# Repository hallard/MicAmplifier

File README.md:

Universal Stereo MIC/Line amplifier for Audio processing with ADC
================================================================

This is a simple board to amplifiy stereo mic or ligne signal to be processed
by a analog entry of a microcontroller.

It can be used for processing audio and lit LED strip for example or whatever,
the input signal can come from electret microphone, standard microphone,
line out or any jack audio output of any device.

Schematics were strongly took and inspired from [coolarduino][1] site 
and the [vu meter 1][2] [vu meter 2][3] topic and schematics

Check out news and other projects on my [blog][4]

Detailed Description
====================

Everything will be documented on my[blog][4]

**Schematic**  

**Board**  

&nbsp;&nbsp;

[1]: http://coolarduino.wordpress.com/
[2]: http://coolarduino.wordpress.com/2012/06/28/stereo-audio-vu-meter-on-arduino/
[3]: http://coolarduino.wordpress.com/2012/07/01/audio-vu-meter-ac-micro-voltmeter-with-extra-wide-dynamic-range-72-db/
[4]: http://hallard.me

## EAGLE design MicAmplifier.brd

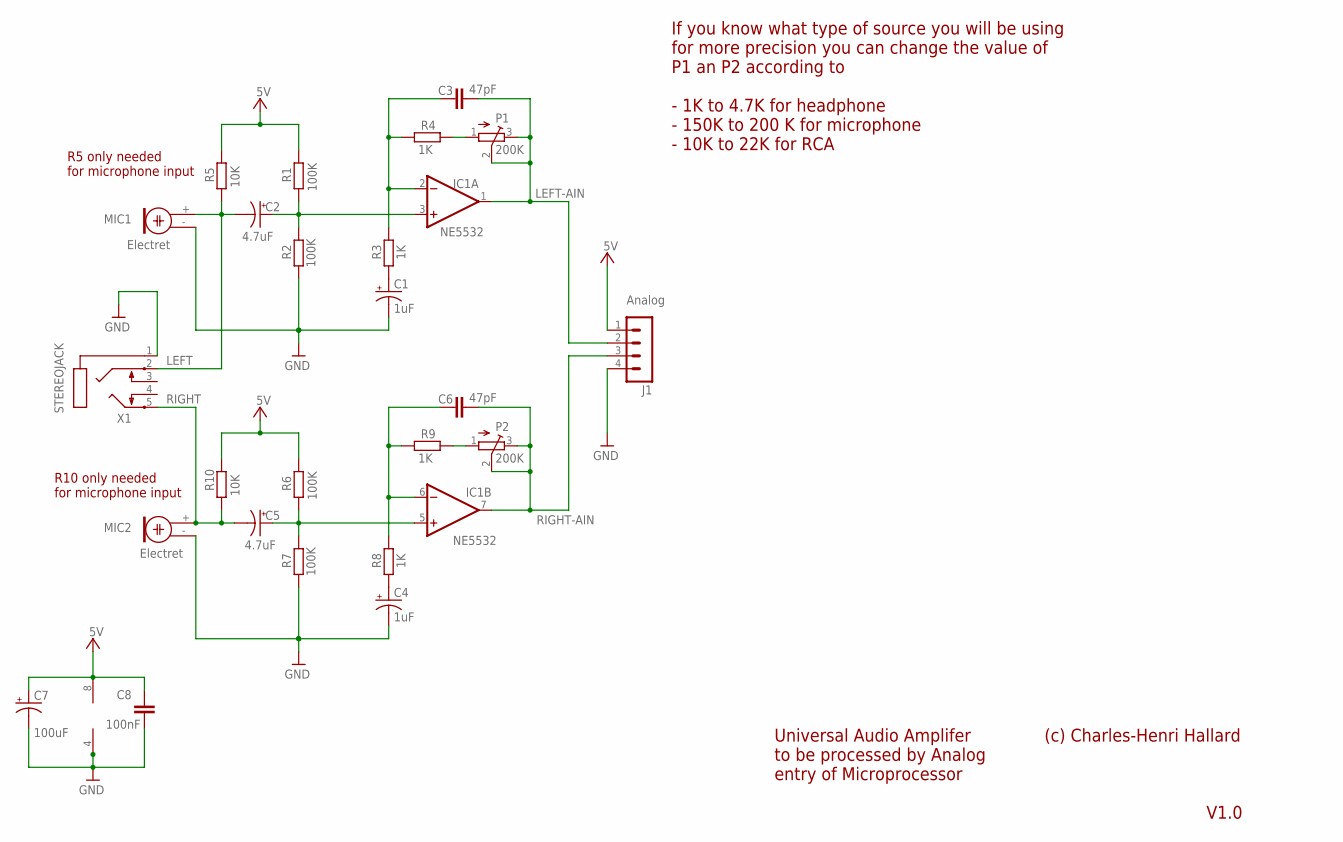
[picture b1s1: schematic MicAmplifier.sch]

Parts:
C1, C4: 1uF; EIA3216
C2, C5: 4.7uF; EIA3216
C3, C6: 47pF; C805
C7: 100uF; CPOL-RADIAL-10UF-25V
C8: 100nF; C805
IC1: NE5532; SO08
J1: Analog; 1X04_LOCK
MIC1, MIC2: Electret; 9.7ELECTRET
P1, P2: 200K; TC33X
R1, R2, R6, R7: 100K; R805
R3, R4, R8, R9: 1K; R805
R5, R10: 10K; R805
X1: STEREOJACK; STX3100

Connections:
+5V: C7.1 (+), C8.2, IC1.8 (V+), J1.1, R1.2, R5.2, R6.2, R10.2
GND: C1.C (-), C4.C (-), C7.2 (-), C8.1, IC1.4 (V-), J1.4, MIC1.- (1), MIC2.- (1), R2.1, R7.1, X1.1
LEFT: C2.C (-), MIC1.+ (2), R5.1, X1.2
LEFT-AIN: C3.2, IC1.1 (OUT), J1.2, P1.2 (S), P1.3 (E)
unnamed: C2.A (+), IC1.3 (+IN), R1.1, R2.2
unnamed: C1.A (+), R3.1
unnamed: C3.1, IC1.2 (-IN), R3.2, R4.1
unnamed: C5.A (+), IC1.5 (+IN), R6.1, R7.2
unnamed: P1.1 (A), R4.2
unnamed: C4.A (+), R8.1
unnamed: C6.1, IC1.6 (-IN), R8.2, R9.1
unnamed: P2.1 (A), R9.2
RIGHT: C5.C (-), MIC2.+ (2), R10.1, X1.5
RIGHT-AIN: C6.2, IC1.7 (OUT), J1.3, P2.2 (S), P2.3 (E)

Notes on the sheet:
Universal Audio Amplifer to be processed by Analog entry of Microprocessor
(c) Charles-Henri Hallard
If you know what type of source you will be using for more precision you can change the value of P1 an P2 according to
- 1K to 4.7K for headphone - 150K to 200 K for microphone - 10K to 22K for RCA
R5 only needed for microphone input
R10 only needed for microphone input
V1.0

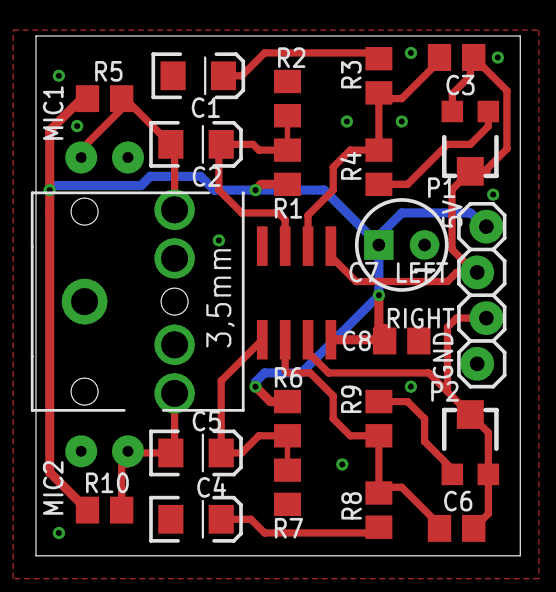
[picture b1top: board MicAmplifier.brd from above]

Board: 2 copper layers, 26.9 x 28.9 mm, 25 parts (0 on the bottom side), 14 nets.

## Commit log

2014-01-22 Resize Image
2014-01-22 Image Resize
2014-01-22 Resize
2014-02-05 Cosmetic Change

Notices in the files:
parts and their libraries:
SparkFun-Passives: Licensing: CC v3.0 Share-Alike You are welcome to use this library for commercial purposes.
